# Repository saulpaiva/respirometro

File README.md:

# **RESPIRÔMETRO**
[Centro de Tecnologia Acadêmica - UFRGS](http://cta.if.ufrgs.br)

**Autor/es:** Béuren Felipe Bechlin

**Licença/s:** GPL v3

---
## Descriçao do projeto

O Respirômetro é um equipamento desenhado para medir a frequência respiratória humana. 
Utilizando um par de termistores, o sinal analógico da respiração é convertido em sinal 
digital que pode então ser processado por um microcontrolador que envia dados para o computador.

---
## Primeiros passos

Para utilização do projeto é necessário uma placa de prototipagem Arduino ou um microcontrolador
ATMEGA com suporte a wiring. Na pasta sources você irá encontrar a pasta Arduino que contém o código
fonte deve estar no microcontrolador, já na pasta python contém os códigos fontes para coleta de dados
que são enviados ao computador via comunicação serial gerando um arquivo de log. Nessa mesma pasta
se encontra o arquivo para análise dos dados que foram salvas com a etapa anterior. Lembrando que os
códigos foram desenvolvidos usando *Python* e para seu funcionando é necessário ter instalado o 
interpretador *Python*.
 
### Usando o projeto

#### Passo 1
Primeiro passo a se realizar é instalar as dependências do projeto em sua máquina, caso utiliza
um sistema operacional baseado em GNU/Linux esse trabalho foi reduzido. Supondo que você está
em um ambiente Linux use o seguinte comando:

Esse passo você irá realizar somente uma vez, como é necessário instalar pacotes e módulos python
em seu computador será necessário a senha de administrador para essas operações.

``` Unix
make setup 
```

Após realizar este comando reinicie seu terminal e então realize o segundo passo.

#### Passo 2
Nessa parte será enviado o software para a placa microcontroladora para isso estamos usando
o framework Platformio, lembrando que o firmware desenvolvido foi feito para microcontroladores
ATMEL como suporte a wiring, como por exemplo Arduinos em geral.

``` Unix
make firmware
```

Ao entrar com esse comando irá se iniciar uma tela para seleção da placa que se está usando, além
da porta usb em que ela está conectada ao computador. Na primeira vez que for enviar o firmaware para
cada tipo de placa será necessário digiar _y_ no terminal para que o platformio instale as dependências
para compilação de cada modelo de placa.

---
Para demais informações e documentação completa visite
[CTA - RESPIRÔMETRO](http://cta.if.ufrgs.br/projects/fisiolog/wiki/Respirômetro)

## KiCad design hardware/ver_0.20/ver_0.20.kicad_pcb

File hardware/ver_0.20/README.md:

# Respirômetro

Documentação referente a placa de circuito impresso versão 0.2.
Versão em dosenvolvimento.

### Resitores(ohm):
* R1 (6) = 7.3k 
* R2 (4) = 10k
* R3 (2) = 100k
* R4 (2) = 2.2k
* R5 (0) = 3.3k (SD shield)
* R6 (0) = 1.8k (SD shield)
* R7 (3) = 220

### Capacitores:
* C1 (2) = 100 uF 16v

### Cartão SD:

Começando por cima chip conectando para a esquerda, ou o NC(não conectado).

1. NC
2. CS/SS
3. MOSI	= 11 Pin
4. GND
5. NC
6. 3.3v
7. SCK/CLK	= 13 Pin
8. GND
9. MISO 	= 12 Pin
10. NC
11. NC

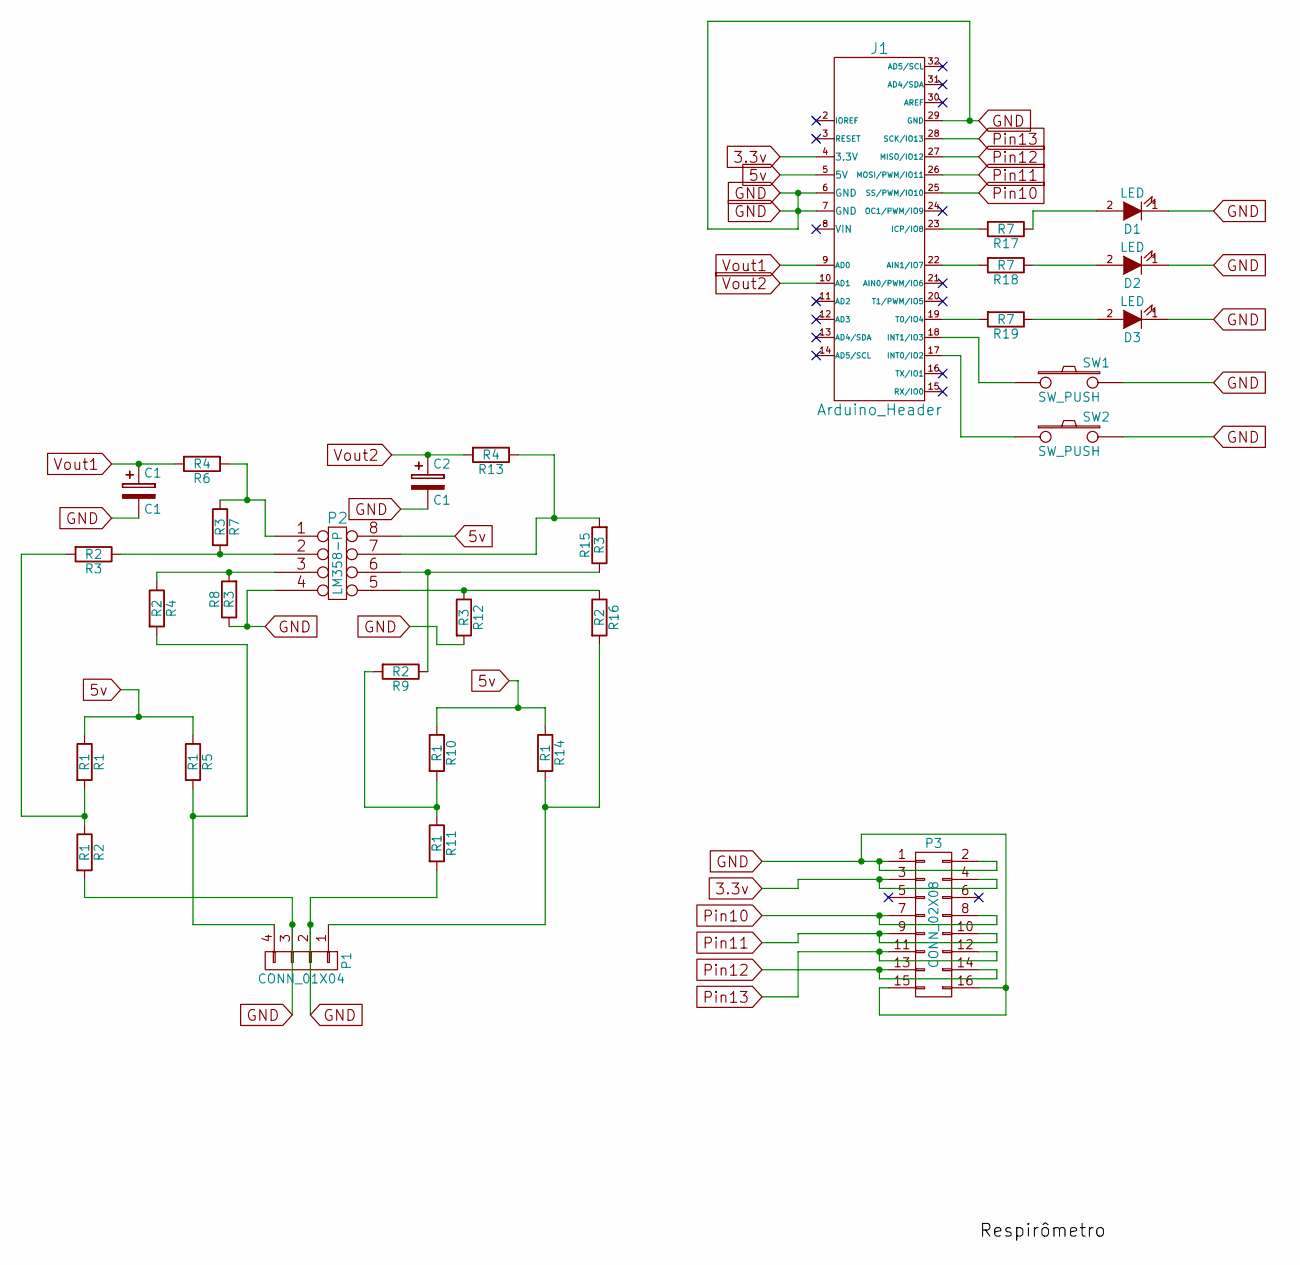
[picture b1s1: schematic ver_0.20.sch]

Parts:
C1, C2: C1; C2V8
D1, D2, D3: LED; LED-5MM
J1: Arduino_Header; arduino_header
P1: CONN_01X04; Socket_Strip_Straight_1x04
P2: LM358-P; DIP-8_W7.62mm_LongPads
P3: CONN_02X08; Socket_Strip_Straight_2x08
R1, R2, R5, R10, R11, R14: R1; Resistor_Horizontal_RM10mm
R3, R4, R9, R16: R2; Resistor_Horizontal_RM10mm
R6, R13: R4; Resistor_Horizontal_RM10mm
R7, R8, R12, R15: R3; Resistor_Horizontal_RM10mm
R17, R18, R19: R7; Resistor_Horizontal_RM10mm
SW1, SW2: SW_PUSH; SW_PUSH_SMALL

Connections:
3.3v: J1.4 (3.3V), P3.3, P3.4
5v: J1.5 (5V), P2.8, R1.1, R5.1, R10.1, R14.1
GND: C1.2, C2.2, D1.1 (K), D2.1 (K), D3.1 (K), J1.6 (GND), J1.7 (GND), J1.29 (GND), P1.2, P1.3, P2.4, P3.1, P3.2, P3.15, P3.16, R2.2, R8.1, R11.2, R12.2, SW1.2, SW2.2
unnamed: D1.2 (A), R17.1
unnamed: D2.2 (A), R18.1
unnamed: D3.2 (A), R19.1
unnamed: J1.17 (INT0/IO2), SW2.1
unnamed: J1.18 (INT1/IO3), SW1.1
unnamed: J1.19 (T0/IO4), R19.2
unnamed: J1.22 (AIN1/IO7), R18.2
unnamed: J1.23 (ICP/IO8), R17.2
unnamed: P1.1, R14.2, R16.2
unnamed: P1.4, R4.2, R5.2
unnamed: P2.1, R6.1, R7.1
unnamed: P2.2, R3.1, R7.2
unnamed: P2.3, R4.1, R8.2
unnamed: P2.5, R12.1, R16.1
unnamed: P2.6, R9.1, R15.1
unnamed: P2.7, R13.1, R15.2
unnamed: R1.2, R2.1, R3.2
unnamed: R9.2, R10.2, R11.1
Pin10: J1.25 (SS/PWM/IO10), P3.7, P3.8
Pin11: J1.26 (MOSI/PWM/IO11), P3.9, P3.10
Pin12: J1.27 (MISO/IO12), P3.13, P3.14
Pin13: J1.28 (SCK/IO13), P3.11, P3.12
Vout1: C1.1, J1.9 (AD0), R6.2
Vout2: C2.1, J1.10 (AD1), R13.2

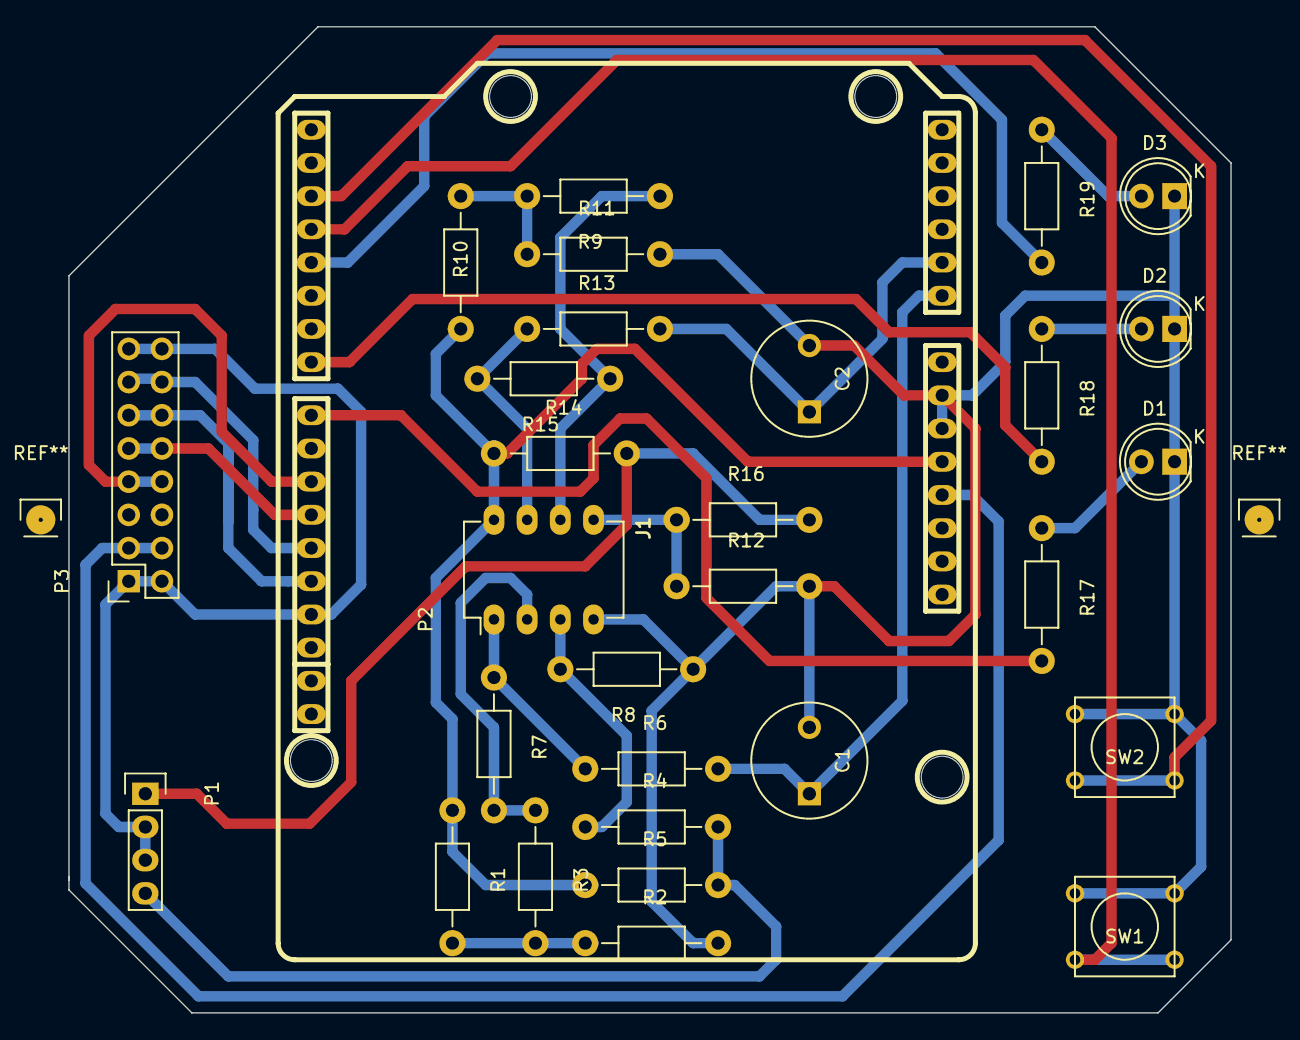
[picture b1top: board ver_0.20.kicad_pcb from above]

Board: 2 copper layers, 88.9 x 75.4 mm, 30 parts (0 on the bottom side), 27 nets.

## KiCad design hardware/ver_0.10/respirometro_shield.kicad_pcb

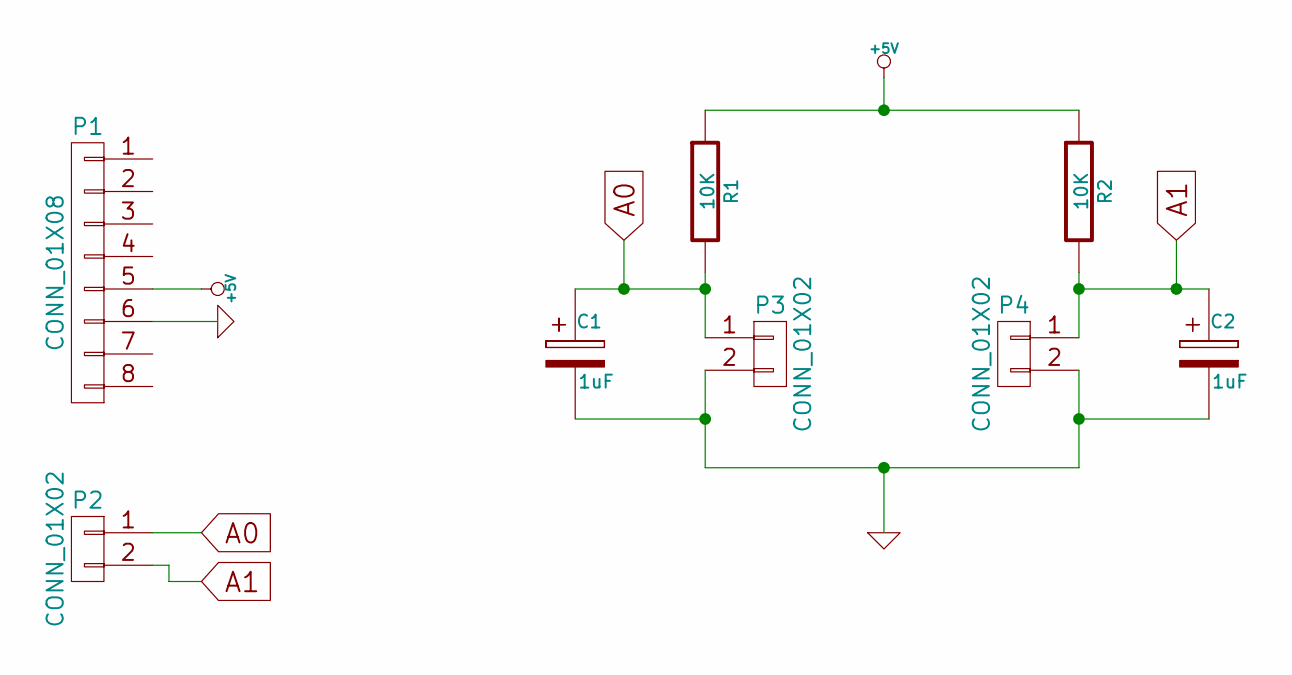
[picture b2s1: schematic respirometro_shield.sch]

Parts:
C1, C2: 1uF; C_Radial_D5_L11_P2.5
P1: CONN_01X08; PINHEAD1-6
P2, P3, P4: CONN_01X02; PINHEAD1-2
R1: 10K; Resistor_Horizontal_RM10mm
R2: 10K; Resistor_Horizontal_RM15mm

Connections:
+5V: P1.5, R1.1, R2.1
A0: C1.1, P2.1, P3.1, R1.2
A1: C2.1, P2.2, P4.1, R2.2
GND: C1.2, C2.2, P1.6, P3.2, P4.2

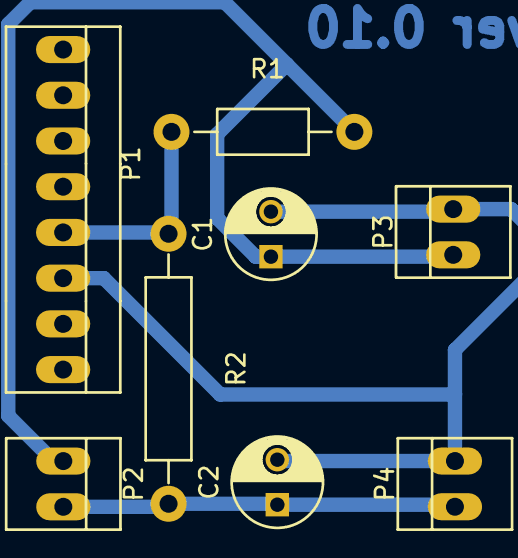
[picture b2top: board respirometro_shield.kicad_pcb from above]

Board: 2 copper layers, 8 parts (0 on the bottom side), 4 nets.

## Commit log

2014-09-30 Primeira Versão para estudo arduino
2014-09-30 Adição arquivo para estudo sobre comunicação serial
2014-09-30 Primeira Versão para estação biométrica
2014-09-30 Alteraçãoes e adição do arquivo para visualização
2014-09-30 Alteração arquivo visualização
2014-10-02 Atualização da estrutura no git e retirada da data no armazenamento
2014-10-09 Versão 09/10/2014, ajusteno foco e introdução do reset dos dados
2014-10-14 Adicionado o estudo do periodo mínimo de operação da visualização
2014-10-16 Armazenamento foi ajustado corrigindo erro de lógica
2014-10-30 Atualização 27/10, adição delays
2014-11-06 Testando FFT-py
2015-03-11 Atualizado o protocolo de envio de dados e adicionado a segunda medida
2015-03-11 Adição analise de fourier
2015-03-19 Iniciando filtros de sinal
2015-04-08 Primeira versão do respirômetro com as duas narinas, estimando a frequência respiratória e tendo como saída um arquivo .png também ajustado bug para encontrar a frequência do arduino
    Conflicts:
    python/visualiza_new.py
2015-04-08 VER_0.0.01: onde temos o armazenamento dos dados e o algoritmo para estimar a frequência respiratório com saída em .png
2015-04-14 Resolução de erros quanto a indices dos vetores
2015-04-16 Atualização de pequenos bugs, ainda sendo necessário correção de erro na quantidade de dados
2015-04-17 Adição de tratamento de erros na entrada da visualização
2015-04-22 Adicionado correção contra mais bugs, tais como baud rate e serial port
2015-04-24 Adição do READ_ME e do shell script, embora tenha bug com o comando python estudando solução
2015-04-27 Ajustado bug na quantidade de argumentos e arrumado o shell script!
2015-04-29 editando o layout e adicionando logo do cta
2015-09-14 Atualizando dependências
2015-11-18 adequando ao modelo
2015-11-18 Formatando o README
2016-02-23 Reorganizando repsitório, adicionando esquemáticos e arquivos para confeccão de uma placa de circuito impresso.
2016-03-11 NEW: scratch sample for using PyQt with matplotlib
2016-03-14 Estudando disposição de itens na tela com pyqt
2016-03-16 Criação de interação e dockW
2016-03-30 Firmware criado para testes e utilidades para a placa versão 0.20
2016-05-16 Criando branch para testes
2016-05-18 ADD: python requeriments, ATT:storeBinData
2016-05-18 MODIFY: firmware , suports 3 reads
2016-05-18 MODIFY:storeBinData adicionando coluna de tempo
2016-05-23 Corrigido visualização e alterado README.md
2016-05-30 Script de coleta finalizado.
2016-06-01 MODIFY: Makefile, coletaScript.py
2016-06-17 ATT: empacotamento e desenpacotamento de dados do respirômetro, read-me com instruções de uso
